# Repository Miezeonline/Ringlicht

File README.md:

# Ringlicht
Ringlicht für Mikroskope oder Bohrmaschinen, erstellt mit KiCAD
erstmal nur ein Test

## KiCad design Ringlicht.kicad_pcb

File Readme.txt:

https://littlemachineshop.com/mobile/bolt_circle.php

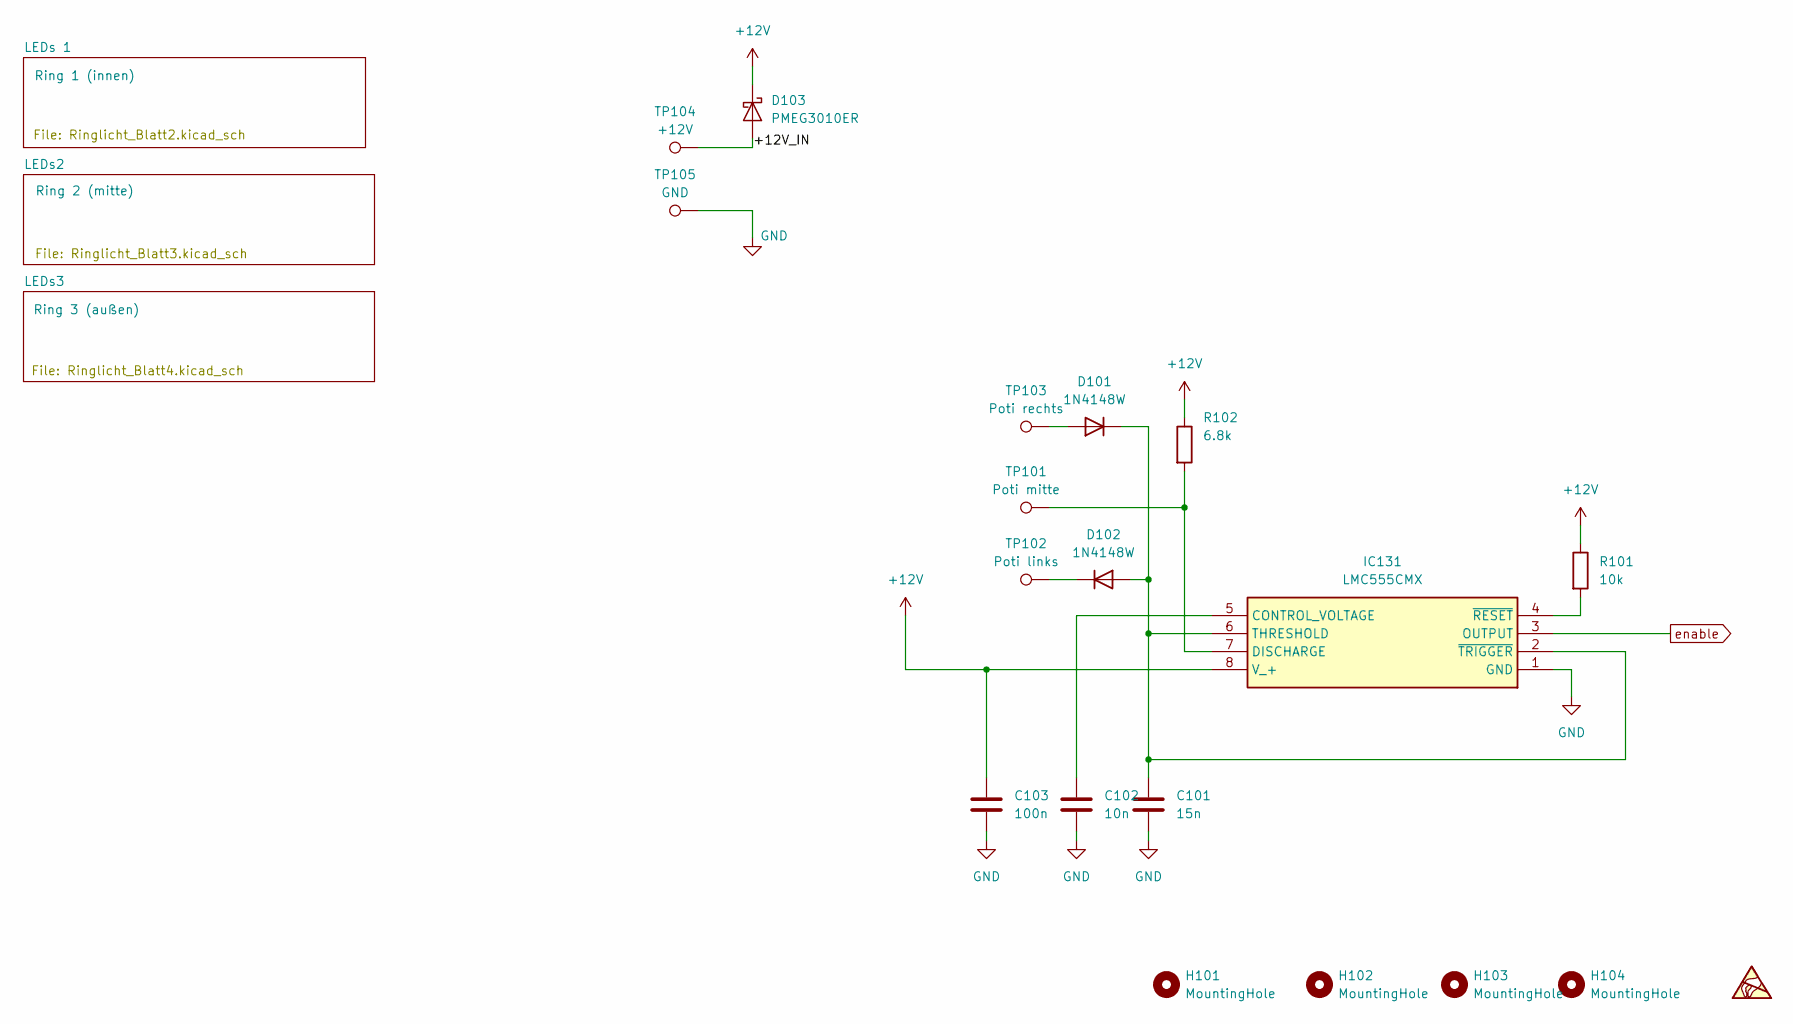
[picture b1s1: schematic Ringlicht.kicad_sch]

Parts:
C101: 15n; C_0603_1608Metric
C102: 10n; C_0603_1608Metric
C103: 100n; C_0603_1608Metric
D101, D102: 1N4148W; D_SOD-123
D103: PMEG3010ER; Nexperia_CFP3_SOD-123W
H101, H102, H103, H104: MountingHole; MountingHole_2.1mm
IC131: LMC555CMX; SOIC127P600X175-8N; Mouser Part Number 926-LMC555CMX
R101: 10k; R_0603_1608Metric
R102: 6.8k; R_0603_1608Metric
TP101: Poti mitte; TestPoint_Pad_2.0x2.0mm
TP102: Poti links; TestPoint_Pad_2.0x2.0mm
TP103: Poti rechts; TestPoint_Pad_2.0x2.0mm
TP104: +12V; TestPoint_Pad_2.0x2.0mm
TP105: GND; TestPoint_Pad_2.0x2.0mm

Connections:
0: C101.2, C102.2, C103.2, IC131.1 (GND), TP105.1; also elsewhere on the board
+12V: C103.1, D103.1 (K), IC131.8 (V_+), R101.1, R102.1; also elsewhere on the board
/+12V_IN: D103.2 (A), TP104.1
unnamed: D101.2 (A), TP103.1
unnamed: C101.1, D101.1 (K), D102.2 (A), IC131.2 (~TRIGGER), IC131.6 (THRESHOLD)
unnamed: D102.1 (K), TP102.1
unnamed: C102.1, IC131.5 (CONTROL_VOLTAGE)
unnamed: IC131.7 (DISCHARGE), R102.2, TP101.1
unnamed: IC131.4 (~RESET), R101.2
enable: IC131.3 (OUTPUT); also elsewhere on the board

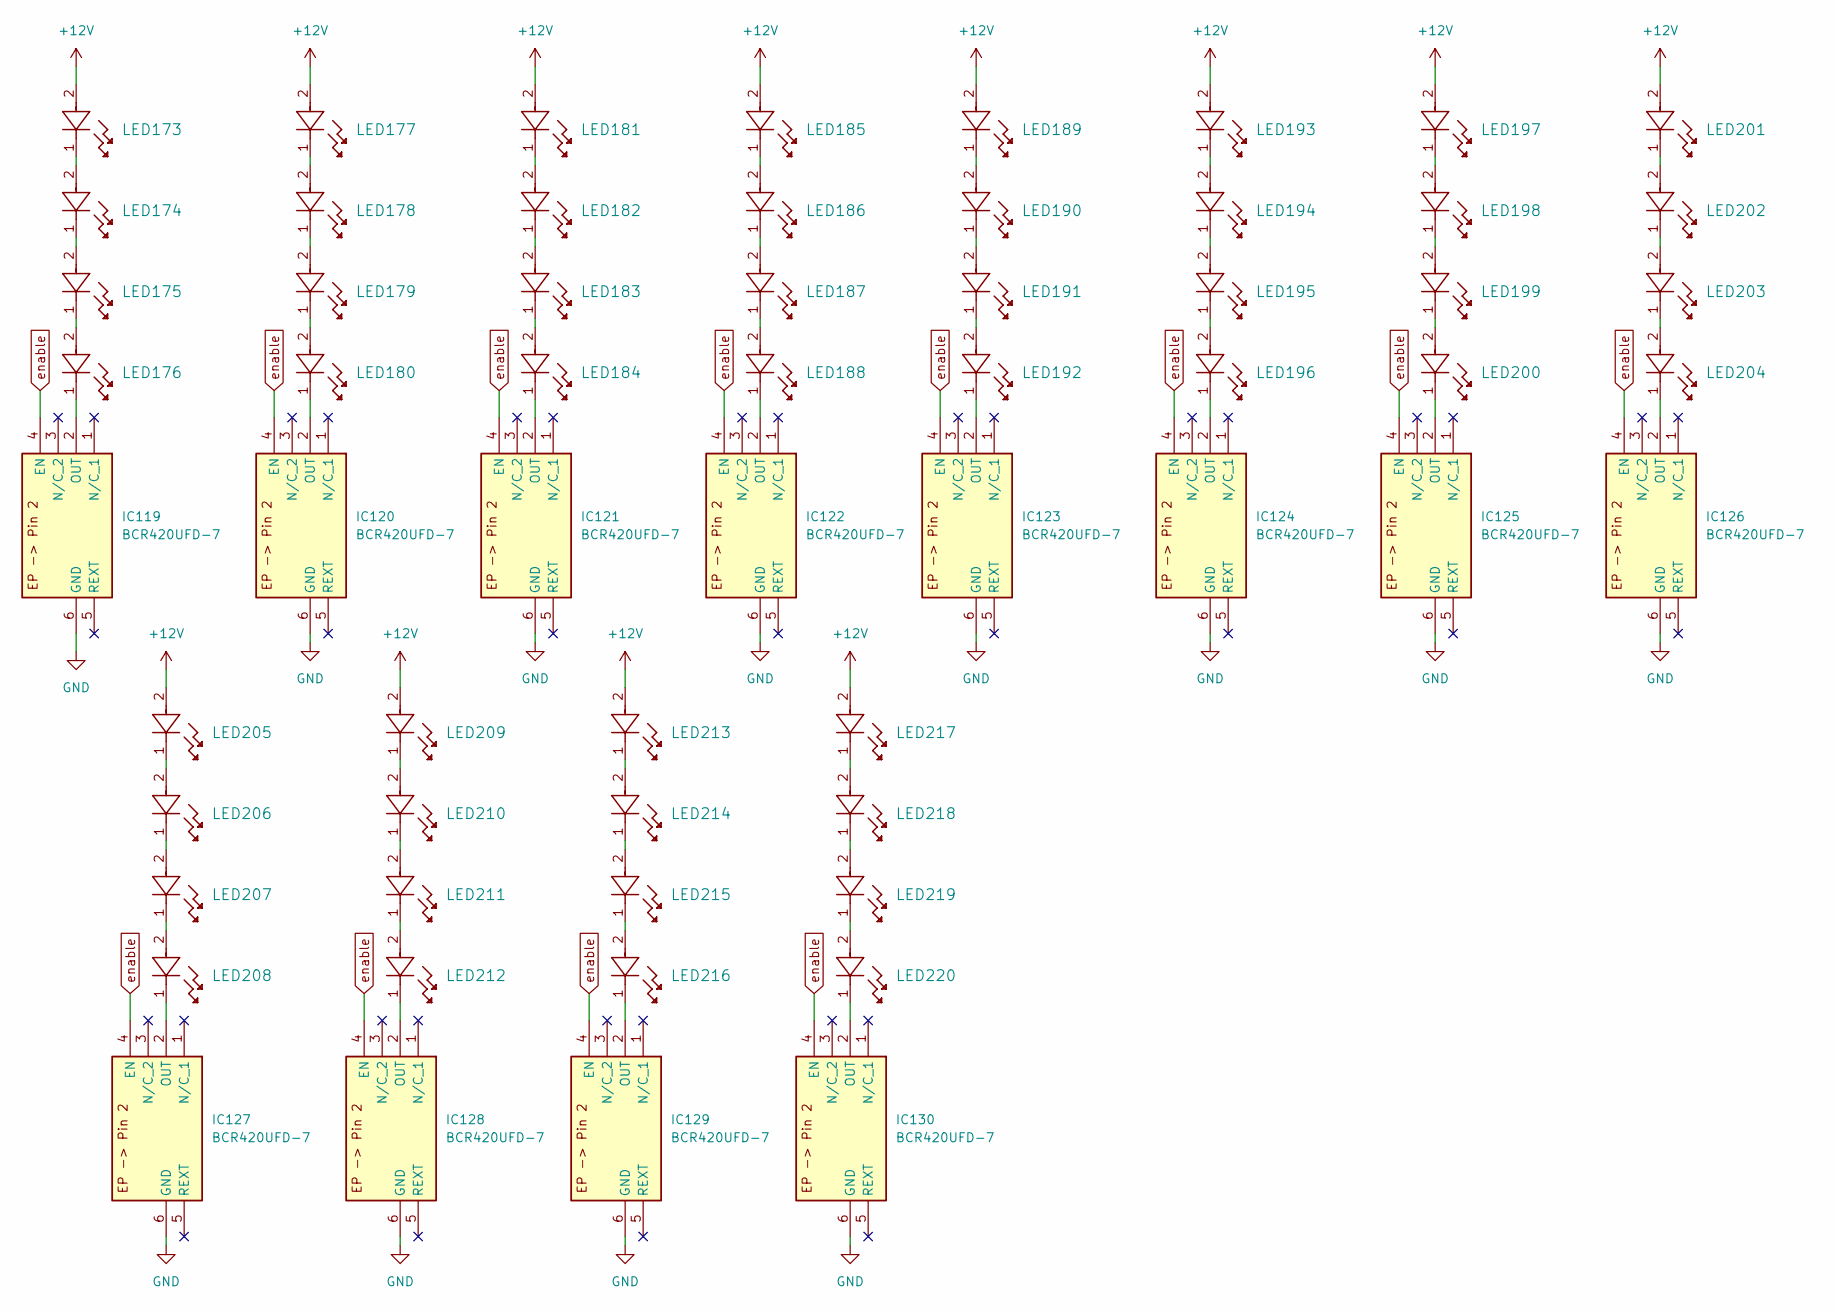
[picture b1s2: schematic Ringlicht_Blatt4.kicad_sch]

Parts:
IC119, IC120, IC121, IC122, IC123, IC124, IC125, IC126, IC127, IC128, IC129, IC130: BCR420UFD-7; AP2301SN7; Mouser Part Number 621-BCR420UFD-7
LED173, LED174, LED175, LED176: ${SIM.PARAMS}; LED_KW DELPS2.RA_OSR
LED177, LED178, LED179, LED180, LED181, LED182, LED183, LED184, LED185, LED186, LED187, LED188, LED189, LED190, LED191, LED192, LED193, LED194, LED195, LED196, LED197, LED198, LED199, LED200, LED201, LED202, LED203, LED204, LED205, LED206, LED207, LED208, LED209, LED210, LED211, LED212, LED213, LED214, LED215, LED216, LED217, LED218, LED219, LED220: KW DELPS2.RA-TIVH-FK0PM0-Z555; LED_KW DELPS2.RA_OSR

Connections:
0: IC119.6 (GND), IC120.6 (GND), IC121.6 (GND), IC122.6 (GND), IC123.6 (GND), IC124.6 (GND), IC125.6 (GND), IC126.6 (GND), IC127.6 (GND), IC128.6 (GND), IC129.6 (GND), IC130.6 (GND); also elsewhere on the board
+12V: LED173.2, LED177.2, LED181.2, LED185.2, LED189.2, LED193.2, LED197.2, LED201.2, LED205.2, LED209.2, LED213.2, LED217.2; also elsewhere on the board
unnamed: IC119.2 (OUT), LED176.1
unnamed: IC120.2 (OUT), LED180.1
unnamed: IC121.2 (OUT), LED184.1
unnamed: IC122.2 (OUT), LED188.1
unnamed: IC123.2 (OUT), LED192.1
unnamed: IC124.2 (OUT), LED196.1
unnamed: IC125.2 (OUT), LED200.1
unnamed: IC126.2 (OUT), LED204.1
unnamed: IC127.2 (OUT), LED208.1
unnamed: IC128.2 (OUT), LED212.1
unnamed: IC129.2 (OUT), LED216.1
unnamed: IC130.2 (OUT), LED220.1
unnamed: LED173.1, LED174.2
unnamed: LED174.1, LED175.2
unnamed: LED175.1, LED176.2
unnamed: LED177.1, LED178.2
unnamed: LED178.1, LED179.2
unnamed: LED179.1, LED180.2
unnamed: LED181.1, LED182.2
unnamed: LED182.1, LED183.2
unnamed: LED183.1, LED184.2
unnamed: LED185.1, LED186.2
unnamed: LED186.1, LED187.2
unnamed: LED187.1, LED188.2
unnamed: LED189.1, LED190.2
unnamed: LED190.1, LED191.2
unnamed: LED191.1, LED192.2
unnamed: LED193.1, LED194.2
unnamed: LED194.1, LED195.2
unnamed: LED195.1, LED196.2
unnamed: LED197.1, LED198.2
unnamed: LED198.1, LED199.2
unnamed: LED199.1, LED200.2
unnamed: LED201.1, LED202.2
unnamed: LED202.1, LED203.2
unnamed: LED203.1, LED204.2
unnamed: LED205.1, LED206.2
unnamed: LED206.1, LED207.2
unnamed: LED207.1, LED208.2
unnamed: LED209.1, LED210.2
unnamed: LED210.1, LED211.2
unnamed: LED211.1, LED212.2
unnamed: LED213.1, LED214.2
unnamed: LED214.1, LED215.2
unnamed: LED215.1, LED216.2
unnamed: LED217.1, LED218.2
unnamed: LED218.1, LED219.2
unnamed: LED219.1, LED220.2
enable: IC119.4 (EN), IC120.4 (EN), IC121.4 (EN), IC122.4 (EN), IC123.4 (EN), IC124.4 (EN), IC125.4 (EN), IC126.4 (EN), IC127.4 (EN), IC128.4 (EN), IC129.4 (EN), IC130.4 (EN); also elsewhere on the board

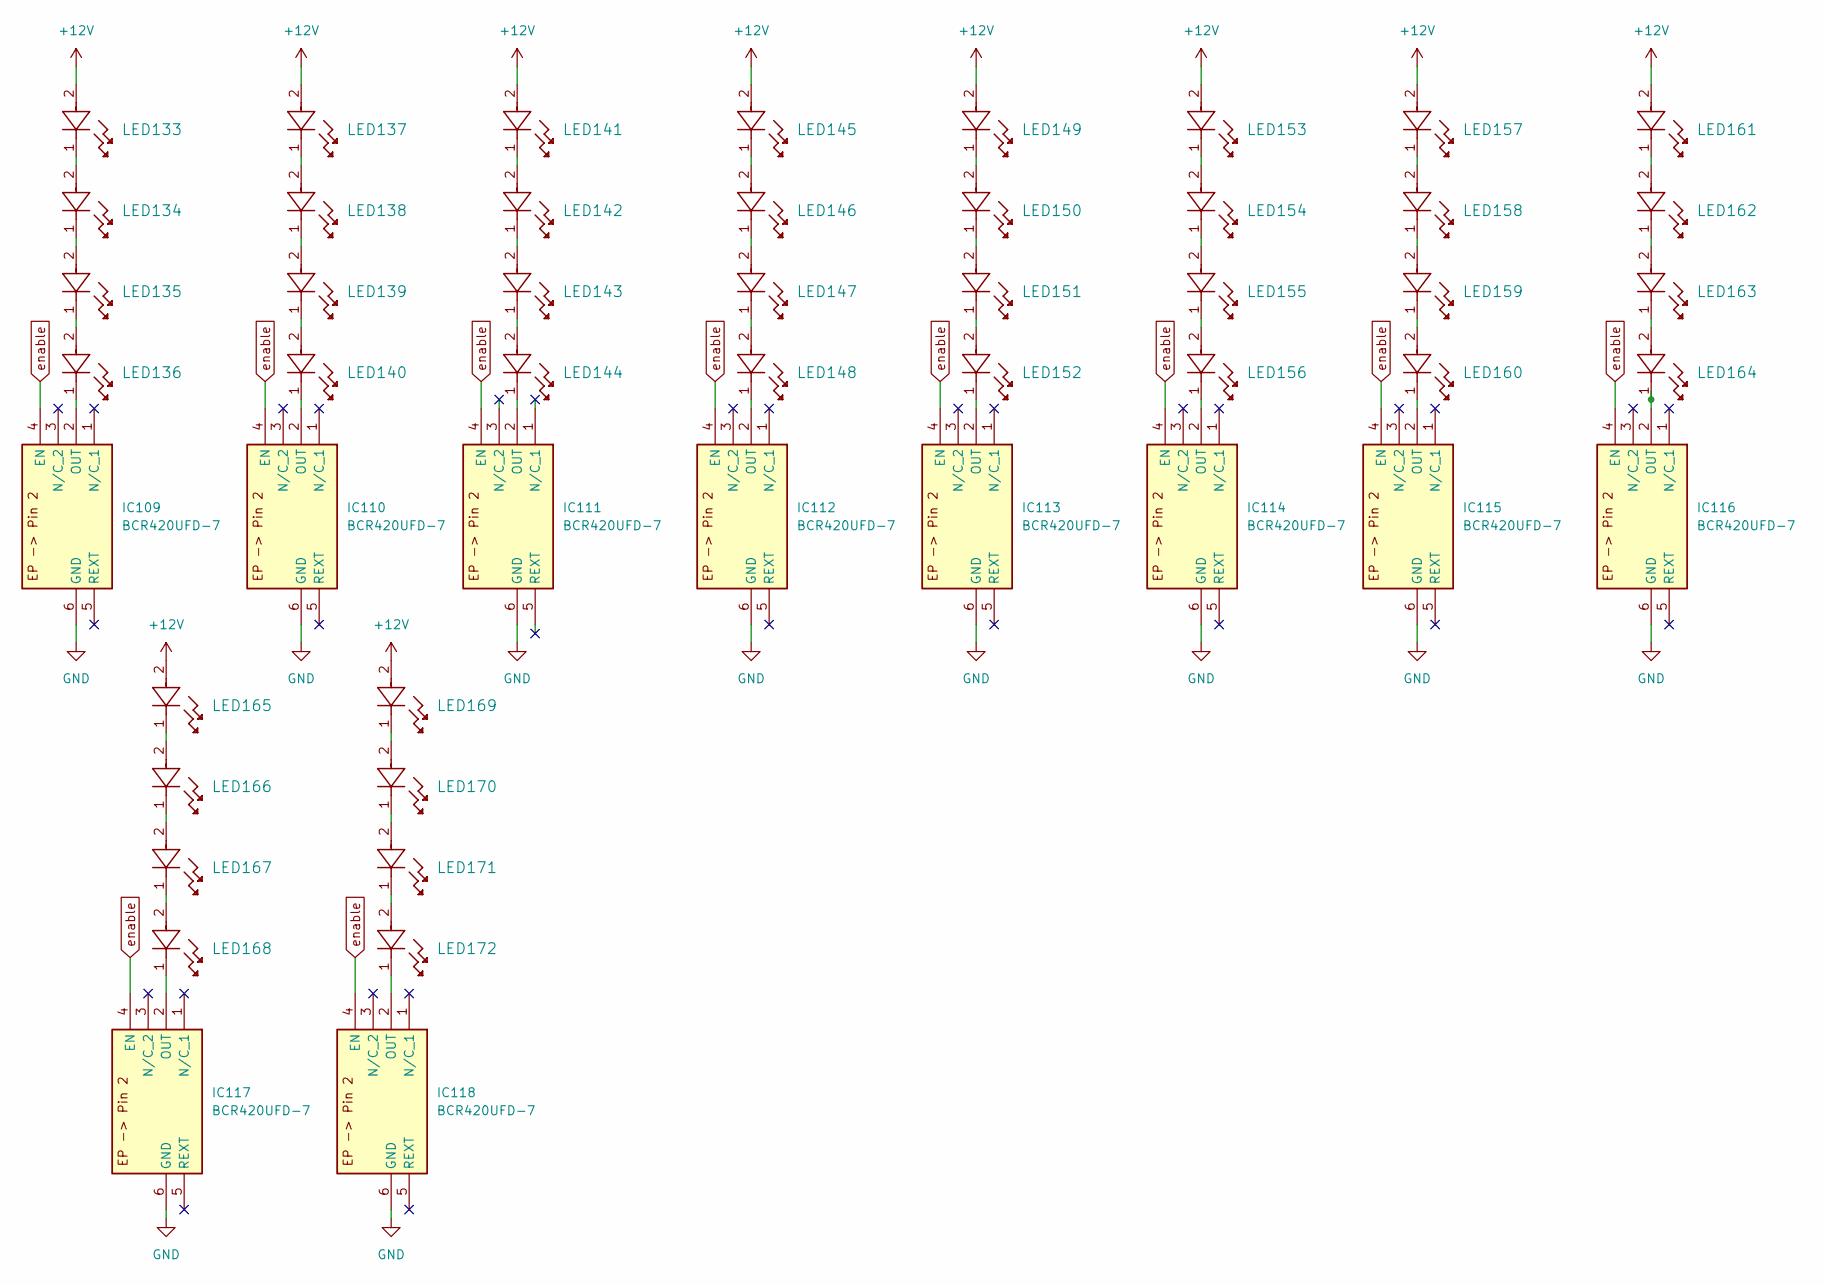
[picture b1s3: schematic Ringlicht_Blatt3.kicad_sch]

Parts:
IC109, IC110, IC111, IC112, IC113, IC114, IC115, IC116, IC117, IC118: BCR420UFD-7; AP2301SN7; Mouser Part Number 621-BCR420UFD-7
LED133, LED134, LED135, LED136, LED137, LED138, LED139, LED140, LED141, LED142, LED143, LED144, LED145, LED146, LED147, LED148, LED149, LED150, LED151, LED152, LED153, LED154, LED155, LED156, LED157, LED158, LED159, LED160, LED161, LED162, LED163, LED164, LED165, LED166, LED167, LED168, LED169, LED170, LED171, LED172: KW DELPS2.RA-TIVH-FK0PM0-Z555; LED_KW DELPS2.RA_OSR

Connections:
0: IC109.6 (GND), IC110.6 (GND), IC111.6 (GND), IC112.6 (GND), IC113.6 (GND), IC114.6 (GND), IC115.6 (GND), IC116.6 (GND), IC117.6 (GND), IC118.6 (GND); also elsewhere on the board
+12V: LED133.2, LED137.2, LED141.2, LED145.2, LED149.2, LED153.2, LED157.2, LED161.2, LED165.2, LED169.2; also elsewhere on the board
unnamed: IC109.2 (OUT), LED136.1
unnamed: IC110.2 (OUT), LED140.1
unnamed: IC111.2 (OUT), LED144.1
unnamed: IC112.2 (OUT), LED148.1
unnamed: IC113.2 (OUT), LED152.1
unnamed: IC114.2 (OUT), LED156.1
unnamed: IC115.2 (OUT), LED160.1
unnamed: IC116.2 (OUT), LED164.1
unnamed: IC117.2 (OUT), LED168.1
unnamed: IC118.2 (OUT), LED172.1
unnamed: LED133.1, LED134.2
unnamed: LED134.1, LED135.2
unnamed: LED135.1, LED136.2
unnamed: LED137.1, LED138.2
unnamed: LED138.1, LED139.2
unnamed: LED139.1, LED140.2
unnamed: LED141.1, LED142.2
unnamed: LED142.1, LED143.2
unnamed: LED143.1, LED144.2
unnamed: LED145.1, LED146.2
unnamed: LED146.1, LED147.2
unnamed: LED147.1, LED148.2
unnamed: LED149.1, LED150.2
unnamed: LED150.1, LED151.2
unnamed: LED151.1, LED152.2
unnamed: LED153.1, LED154.2
unnamed: LED154.1, LED155.2
unnamed: LED155.1, LED156.2
unnamed: LED157.1, LED158.2
unnamed: LED158.1, LED159.2
unnamed: LED159.1, LED160.2
unnamed: LED161.1, LED162.2
unnamed: LED162.1, LED163.2
unnamed: LED163.1, LED164.2
unnamed: LED165.1, LED166.2
unnamed: LED166.1, LED167.2
unnamed: LED167.1, LED168.2
unnamed: LED169.1, LED170.2
unnamed: LED170.1, LED171.2
unnamed: LED171.1, LED172.2
enable: IC109.4 (EN), IC110.4 (EN), IC111.4 (EN), IC112.4 (EN), IC113.4 (EN), IC114.4 (EN), IC115.4 (EN), IC116.4 (EN), IC117.4 (EN), IC118.4 (EN); also elsewhere on the board

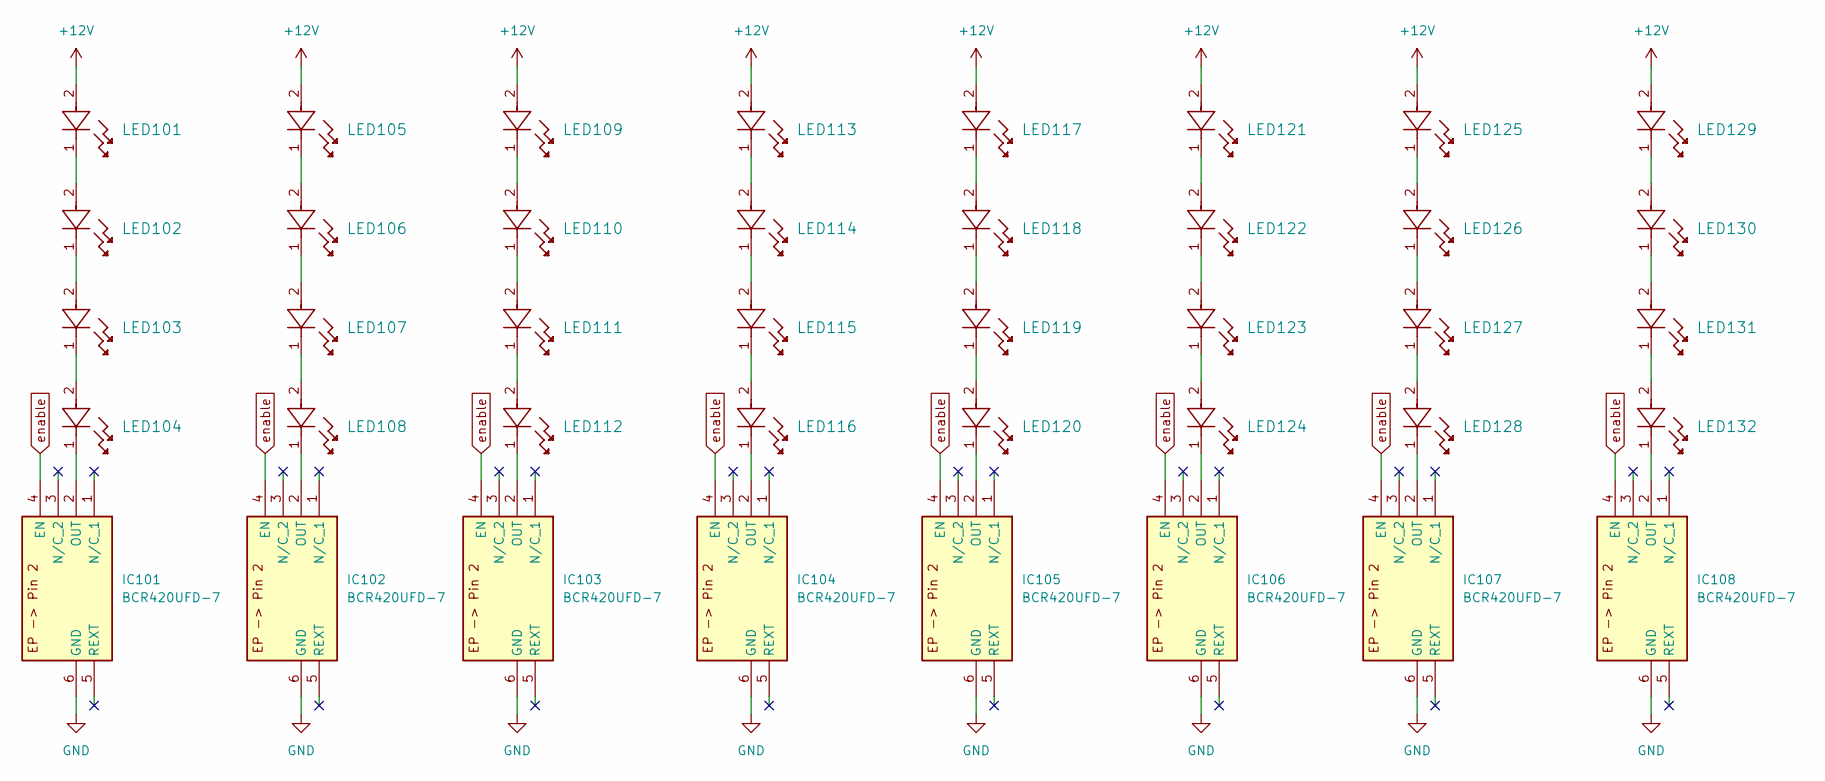
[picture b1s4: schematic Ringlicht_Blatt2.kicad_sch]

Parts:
IC101, IC102, IC103, IC104, IC105, IC106, IC107, IC108: BCR420UFD-7; AP2301SN7; Mouser Part Number 621-BCR420UFD-7
LED101, LED102, LED103, LED104, LED105, LED106, LED107, LED108, LED109, LED110, LED111, LED112, LED116: ${SIM.PARAMS}; LED_KW DELPS2.RA_OSR
LED113, LED114, LED115, LED117, LED118, LED119, LED120, LED121, LED122, LED123, LED124, LED125, LED126, LED127, LED128, LED129, LED130, LED131, LED132: KW DELPS2.RA-TIVH-FK0PM0-Z555; LED_KW DELPS2.RA_OSR

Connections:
0: IC101.6 (GND), IC102.6 (GND), IC103.6 (GND), IC104.6 (GND), IC105.6 (GND), IC106.6 (GND), IC107.6 (GND), IC108.6 (GND); also elsewhere on the board
+12V: LED101.2, LED105.2, LED109.2, LED113.2, LED117.2, LED121.2, LED125.2, LED129.2; also elsewhere on the board
unnamed: IC101.2 (OUT), LED104.1
unnamed: IC102.2 (OUT), LED108.1
unnamed: IC103.2 (OUT), LED112.1
unnamed: IC104.2 (OUT), LED116.1
unnamed: IC105.2 (OUT), LED120.1
unnamed: IC106.2 (OUT), LED124.1
unnamed: IC107.2 (OUT), LED128.1
unnamed: IC108.2 (OUT), LED132.1
unnamed: LED101.1, LED102.2
unnamed: LED102.1, LED103.2
unnamed: LED103.1, LED104.2
unnamed: LED105.1, LED106.2
unnamed: LED106.1, LED107.2
unnamed: LED107.1, LED108.2
unnamed: LED109.1, LED110.2
unnamed: LED110.1, LED111.2
unnamed: LED111.1, LED112.2
unnamed: LED113.1, LED114.2
unnamed: LED114.1, LED115.2
unnamed: LED115.1, LED116.2
unnamed: LED117.1, LED118.2
unnamed: LED118.1, LED119.2
unnamed: LED119.1, LED120.2
unnamed: LED121.1, LED122.2
unnamed: LED122.1, LED123.2
unnamed: LED123.1, LED124.2
unnamed: LED125.1, LED126.2
unnamed: LED126.1, LED127.2
unnamed: LED127.1, LED128.2
unnamed: LED129.1, LED130.2
unnamed: LED130.1, LED131.2
unnamed: LED131.1, LED132.2
enable: IC101.4 (EN), IC102.4 (EN), IC103.4 (EN), IC104.4 (EN), IC105.4 (EN), IC106.4 (EN), IC107.4 (EN), IC108.4 (EN); also elsewhere on the board

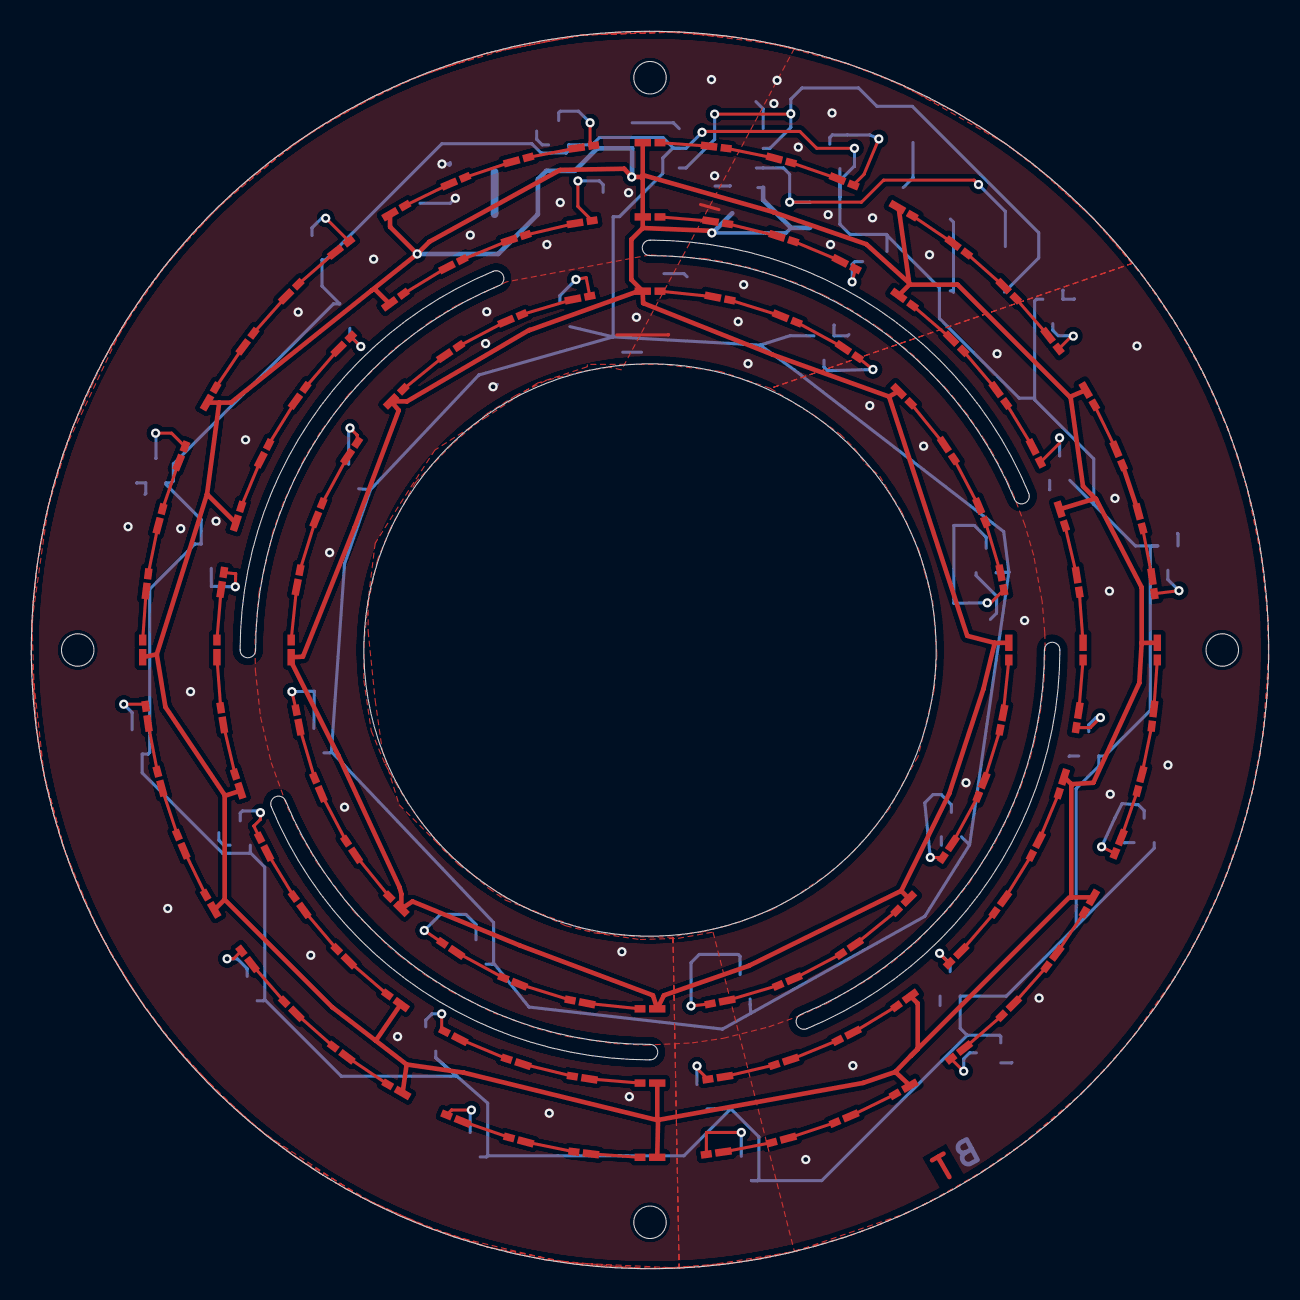
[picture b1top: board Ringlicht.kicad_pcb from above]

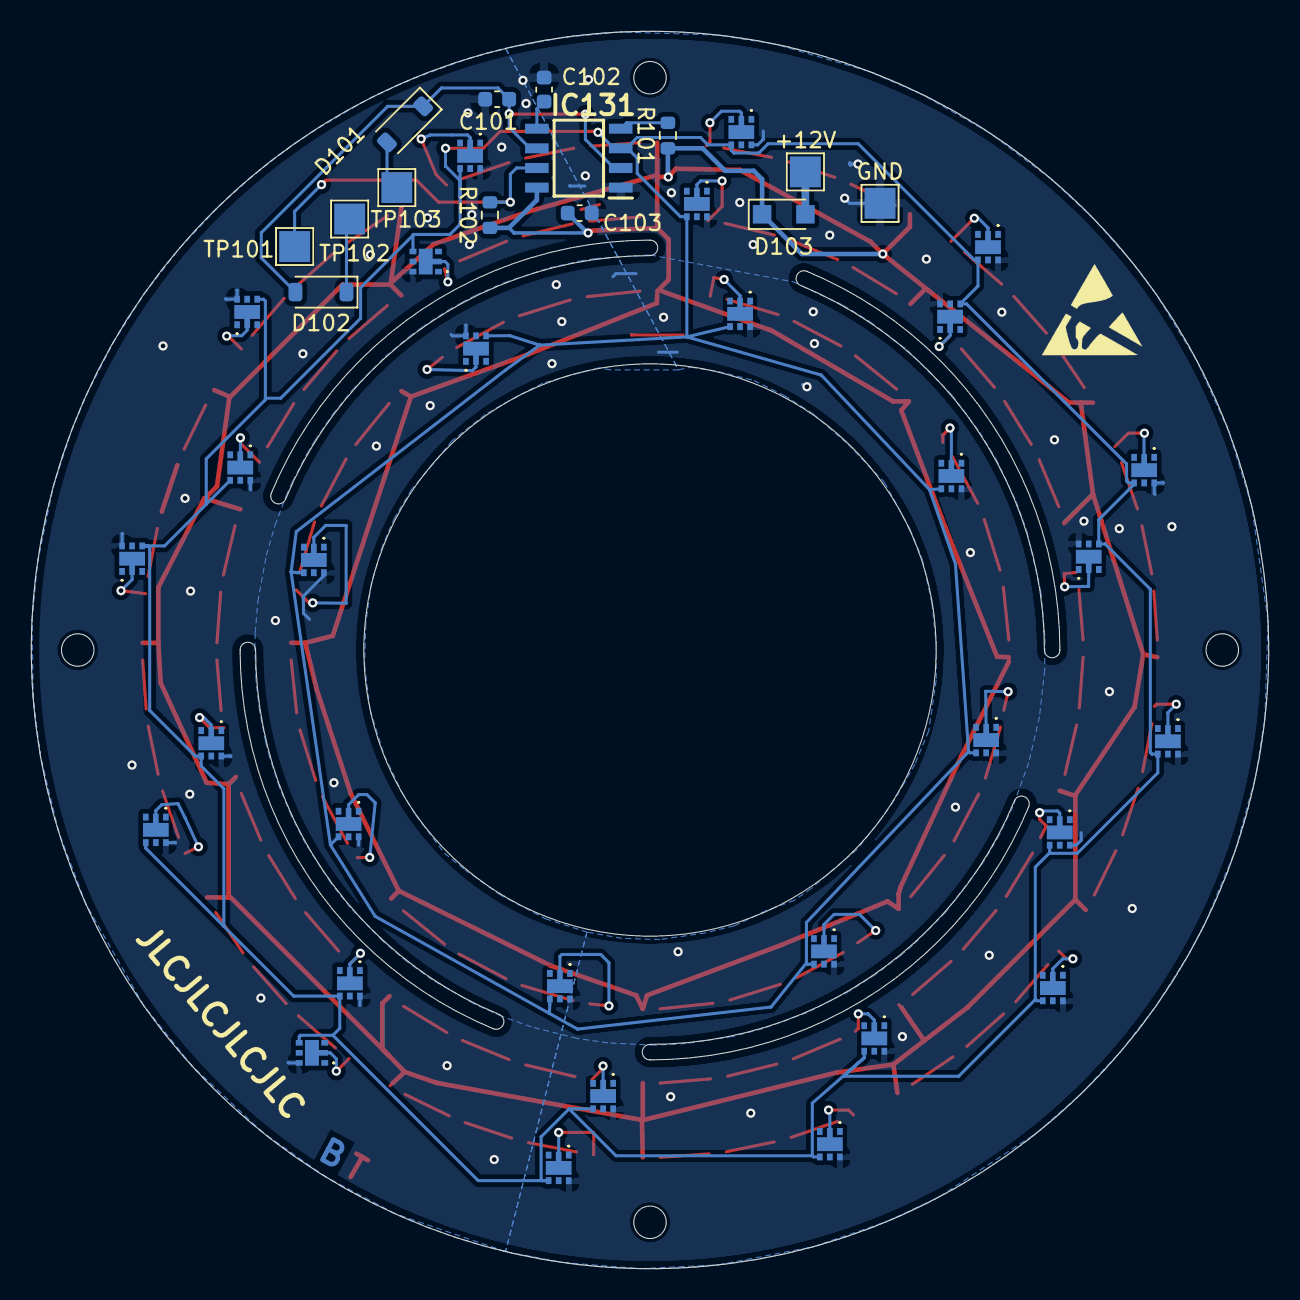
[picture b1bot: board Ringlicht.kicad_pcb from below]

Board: 2 copper layers, 80.0 x 80.0 mm, 168 parts (44 on the bottom side), 130 nets.

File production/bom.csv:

Designator,Footprint,Quantity,Value,LCSC Part #
"C101, C102",0603,2,10n,
C103,0603,1,100n,
"D101, D102",D_SOD-123,2,1N4148W,
D103,Nexperia_CFP3_SOD-123W,1,PMEG3010ER,
"IC101, IC102, IC103, IC104, IC105, IC106, IC107, IC108, IC109, IC110, IC111, IC112, IC113, IC114, IC115, IC116, IC117, IC118, IC119, IC120, IC121, IC122, IC123, IC124, IC125, IC126, IC127, IC128, IC129, IC130",AP2301SN7,30,BCR420UFD-7,
IC131,SOIC127P600X175-8N,1,LMC555CMX,
"LED101, LED102, LED103, LED104, LED105, LED106, LED107, LED108, LED109, LED110, LED111, LED112, LED113, LED114, LED115, LED116, LED117, LED118, LED119, LED120, LED121, LED122, LED123, LED124, LED125, LED126, LED127, LED128, LED129, LED130, LED131, LED132, LED133, LED134, LED135, LED136, LED137, LED138, LED139, LED140, LED141, LED142, LED143, LED144, LED145, LED146, LED147, LED148, LED149, LED150, LED151, LED152, LED153, LED154, LED155, LED156, LED157, LED158, LED159, LED160, LED161, LED162, LED163, LED164, LED165, LED166, LED167, LED168, LED169, LED170, LED171, LED172, LED177, LED178, LED179, LED180, LED181, LED182, LED183, LED184, LED185, LED186, LED187, LED188, LED189, LED190, LED191, LED192, LED193, LED194, LED195, LED196, LED197, LED198, LED199, LED200, LED201, LED202, LED203, LED204, LED205, LED206, LED207, LED208, LED209, LED210, LED211, LED212, LED213, LED214, LED215, LED216, LED217, LED218, LED219, LED220",LED_KW DELPS2.RA_OSR,116,KW DELPS2.RA-TIVH-FK0PM0-Z555,
"LED173, LED174, LED175, LED176",LED_KW DELPS2.RA_OSR,4,~,
R101,0603,1,10k,
R102,0603,1,1k,

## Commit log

2025-12-18 Übernahme Altdaten, LP ok
